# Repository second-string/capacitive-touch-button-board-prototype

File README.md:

# capacitive-touch-button-board-prototype

This repo contains two designs for prototype PCBs for testing different capacitive touch button styles and different reverse-mounted LED colors and styles. While version 1.1 was indeed fabbed, built, and works, these files are made public only for reference. **Do not expect to build these designs with no changes and have everything working for you**.

Version 1.0 is the full 6x6 version of the board. It all fabrication outputs were generated, but the board was never fabbed due to cost.
Version 1.1 is the same as 1.0 but with the top 3 rows of buttons removed to simplify the design physical size and part cost.   

There is a schematic PDF and PCB layer prints PDF in the version 1.1 directory if you do not have KiCad. Version 1.1 that was built also contains generated Excel and interactive boms in its main directory or the `bom/` directory.

Find the custom capacitive touch footprints in the `symbols_and_footprints/` directory of each hardware version.

There is test firmware for version 1.1 in `button-board_rev_1_1/bringup_firmware/`. **NOTE:** This firmware is sloppy, terribly written, inefficient, and everything is hardcoded. It is only included as a reference, do not think that this will work for you out of the box.

Videos of example behavior are in the `img/` directory.

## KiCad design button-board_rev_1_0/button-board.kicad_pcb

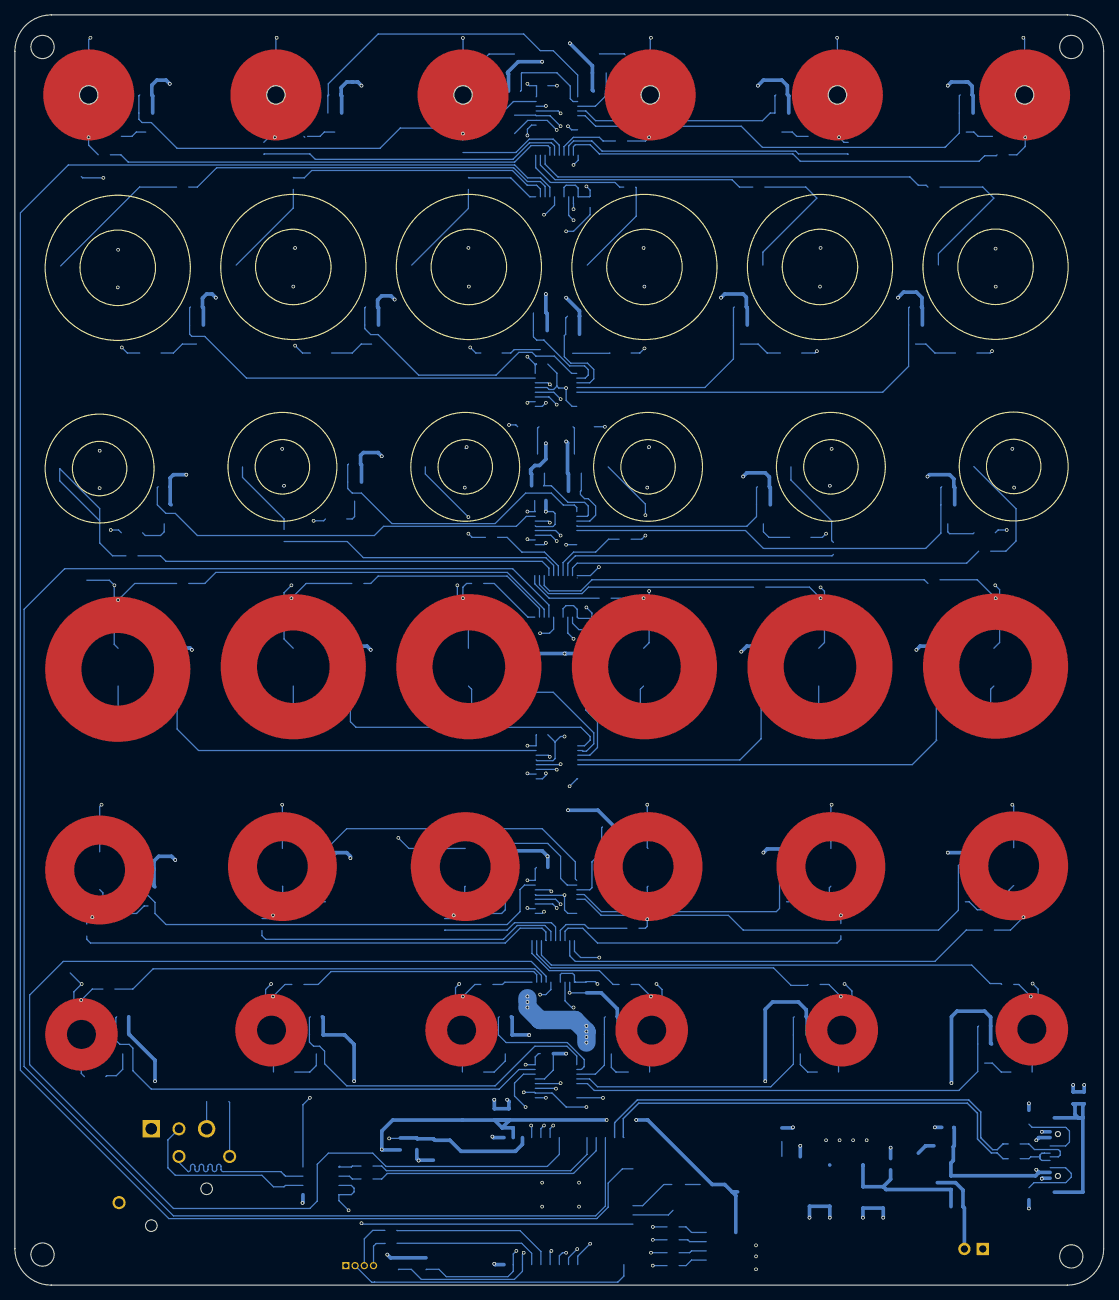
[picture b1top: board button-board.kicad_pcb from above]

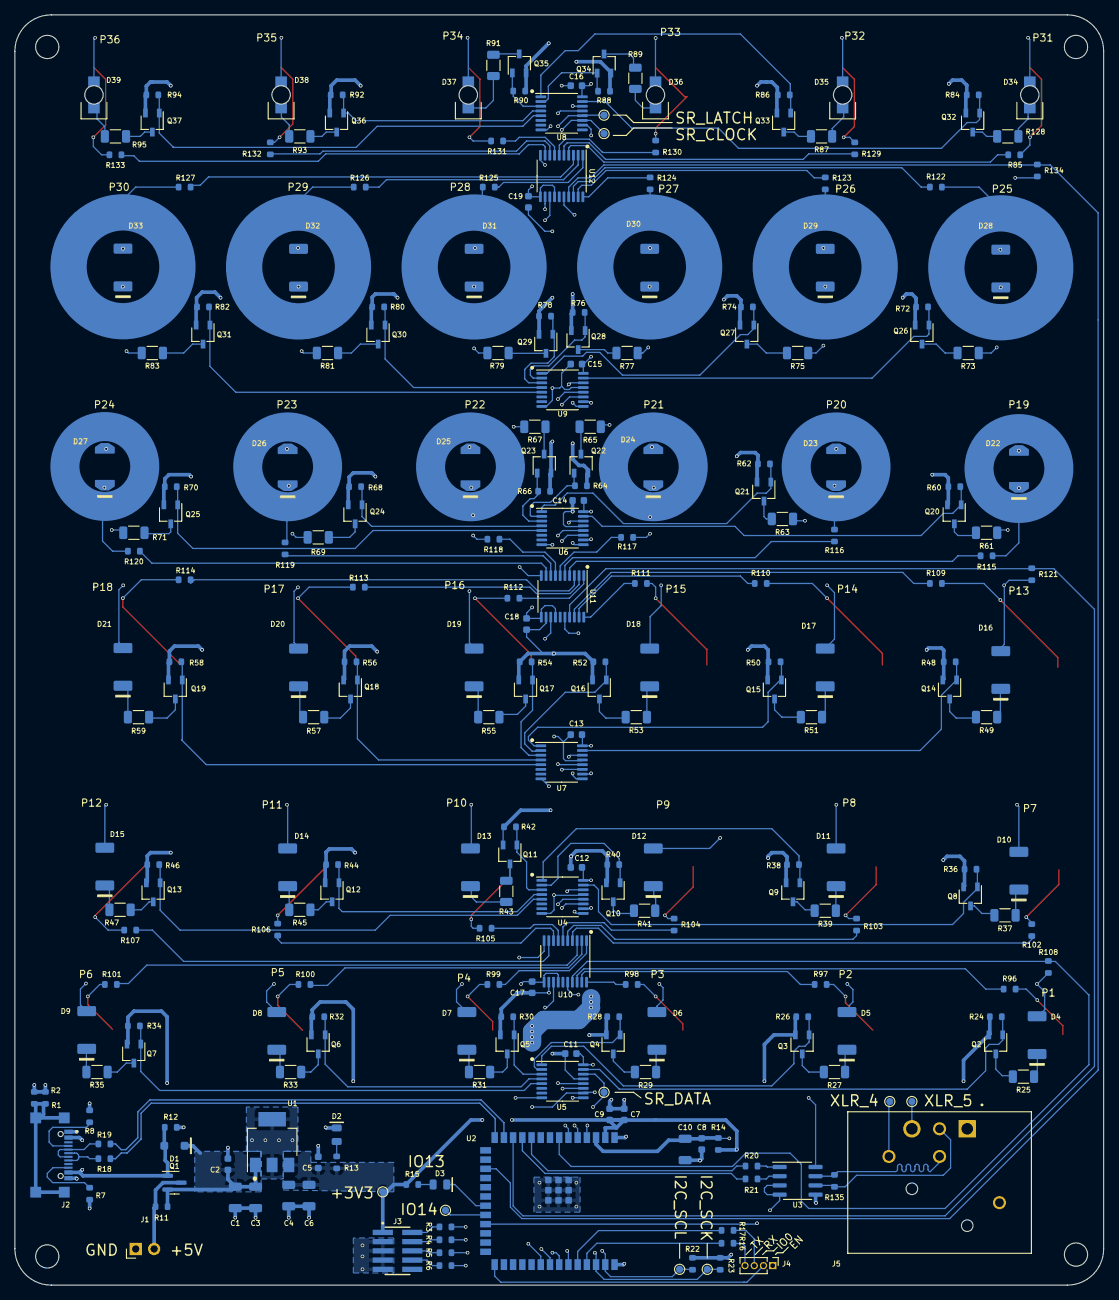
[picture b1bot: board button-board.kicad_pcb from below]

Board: 4 copper layers, 150.0 x 175.0 mm, 294 parts (254 on the bottom side), 232 nets.

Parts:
C1, C3, C6, C10: 10uF; C_1206_3216Metric
C2, C5, C9: 1uF; C_0603_1608Metric
C4: 22uF; C_1206_3216Metric
C7, C8, C11, C12, C13, C14, C15, C16, C17, C18, C19: 0.1uF; C_0603_1608Metric
D1: D; D_SOD-123F
D2, D3: LED; D_0805_2012Metric
D4, D5, D6, D7, D8, D9, D10, D11, D12, D13, D14, D15, D16, D17, D18, D19, D20, D21, D28, D29, D30, D31, D32, D33: LED; LED_SunLED_XZ_Reverse_Mount
D22, D23, D24, D25, D26, D27: LED; LED_SunLED_XZ_Reverse_Mount_Cut_Pads
D34, D35, D36, D37, D38, D39: LED; LED_LTST-C230K
H1, H2, H3, H4: MountingHole; MountingHole_3.2mm_M3
J1: Screw_Terminal_01x02; PinHeader_1x02_P2.54mm_Horizontal
J2: USB_C_Receptacle_USB2.0_EDITED; AMPHENOL_GSB1C41110SSHR
J3: FTSH-105-01-S-DV-TR; SAMTEC_FTSH-105-01-S-DV-TR
J4: Conn_01x04; PinHeader_1x04_P1.27mm_Vertical
J5: XLR5_Ground; NEUTRIK_NC5FAH
P1, P2, P3, P4, P5, P6: Cap_Touch_Ring_Small
P7, P8, P9, P10, P11, P12: Cap_Touch_Ring_Medium
P13, P14, P15, P16, P17, P18: Cap_Touch_Ring_Large
P19, P20, P21, P22, P23, P24: Cap_Touch_Ring_Medium_Bottom
P25, P26, P27, P28, P29, P30: Cap_Touch_Ring_Large_Bottom
P31, P32, P33, P34, P35, P36: Cap_Touch_Ring_Cutout
Q1: PMOS; SOT-23
Q2, Q3, Q4, Q5, Q6, Q7, Q8, Q9, Q10, Q11, Q12, Q13, Q14, Q15, Q16, Q17, Q18, Q19, Q20, Q21, Q22, Q23, Q24, Q25, Q26, Q27, Q28, Q29, Q30, Q31, Q32, Q33, Q34, Q35, Q36, Q37: NMOS; TSOT-23
R1, R2, R11, R16, R17, R18, R19, R20, R21: 0R; R_0603_1608Metric
R3, R4, R5, R6: R; R_0603_1608Metric
R7, R8: 5k1; R_0603_1608Metric
R12: 100k; R_0603_1608Metric
R13, R15: 3.3k-8k; R_0603_1608Metric
R14, R22, R23, R24, R26, R28, R30, R32, R34, R36, R38, R40, R42, R44, R46, R48, R50, R52, R54, R56, R58, R60, R62, R64, R66, R68, R70, R72, R74, R76, R78, R80, R82, R84, R86, R88, R90, R92, R94, R96, R97, R98, R99, R100, R101, R102, R103, R104, R105, R106, R107, R109, R110, R111, R112, R113, R114, R115, R116, R117, R118, R119, R120, R122, R123, R124, R125, R126, R127, R128, R129, R130, R131, R132, R133: 10k; R_0603_1608Metric
R25, R27, R29, R31, R33, R35, R37, R39, R41, R43, R45, R47, R49, R51, R53, R55, R57, R59, R61, R63, R65, R67, R69, R71, R73, R75, R77, R79, R81, R83, R85, R87, R89, R91, R93, R95: 470R 1/2W; R_1206_3216Metric
R108, R121, R134: 47k; R_0603_1608Metric
R135: 120R; R_0603_1608Metric
TP1, TP2: TestPoint; TestPoint_Pad_D1.0mm
TP3: 3V3; TestPoint_Pad_D1.0mm
TP4: IO14; TestPoint_Pad_D1.0mm
TP5: LATCH; TestPoint_Pad_D1.0mm
TP6: CLOCK; TestPoint_Pad_D1.0mm
TP7: DATA; TestPoint_Pad_D1.0mm
TP8: SCL; TestPoint_Pad_D1.0mm
TP9: SCK; TestPoint_Pad_D1.0mm
U1: AZ1117CH2-3.3; SOT-223
U2: ESP32-S3-WROOM-1
U3: SP3485CN; SOIC-8_3.9x4.9mm_P1.27mm
U4, U5, U6, U7, U8, U9: 74HC595; TSSOP-16_4.4x5mm_P0.65mm
U10, U11, U12: AT42QT2120-SU; TSSOP-20_4.4x6.5mm_P0.65mm

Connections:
+3V3: C4.1, C5.1, C6.1, C7.1, C9.1, J3.01, R13.1, R14.1, R15.1, R22.1, R23.1, TP3.1, U1.3 (VO), U2.2 (3V3)
+5V: C11.1, C12.1, C13.1, C14.1, C15.1, C16.1, C17.1, C18.1, C19.1, D4.2 (A), D5.2 (A), D6.2 (A), D7.2 (A), D8.2 (A), D9.2 (A), D10.2 (A), D11.2 (A), D12.2 (A), D13.2 (A), D14.2 (A), D15.2 (A), D16.2 (A), D17.2 (A), D18.2 (A), D19.2 (A), D20.2 (A), D21.2 (A), D22.2 (A), D23.2 (A), D24.2 (A), D25.2 (A), D26.2 (A), D27.2 (A), D28.2 (A), D29.2 (A), D30.2 (A), D31.2 (A), D32.2 (A), D33.2 (A), D34.2 (A), D35.2 (A), D36.2 (A), D37.2 (A), D38.2 (A), D39.2 (A), J1.2, Q1.3 (D), R11.1, R108.1, R121.1, R134.1, U3.8 (VCC), U4.10 (~SRCLR), U4.16 (VCC), U5.10 (~SRCLR), U5.16 (VCC), U6.10 (~SRCLR), U6.16 (VCC), U7.10 (~SRCLR), U7.16 (VCC), U8.10 (~SRCLR), U8.16 (VCC), U9.10 (~SRCLR), U9.16 (VCC), U10.11 (VDD), U10.14 (~RESET), U11.11 (VDD), U11.14 (~RESET), U12.11 (VDD), U12.14 (~RESET)
/control/CAP_CHANGE.0: R108.2, U2.7 (GPIO7/TOUCH7/ADC1_CH6), U10.17 (~CHANGE)
/control/CAP_CHANGE.1: R121.2, U2.12 (GPIO8/TOUCH8/ADC1_CH7/SUBSPICS1), U11.17 (~CHANGE)
/control/CAP_CHANGE.2: R134.2, U2.17 (GPIO9/TOUCH9/ADC1_CH8/FSPIHD/SUBSPIHD), U12.17 (~CHANGE)
/control/DMX.N: J5.2, R135.1, U3.7 (B)
/control/DMX.P: J5.3, R135.2, U3.6 (A)
/control/ESP_IO13: D3.1 (K), U2.21 (GPIO13/TOUCH13/ADC2_CH2/FSPIQ/FSPIIO7/S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)
/control/ESP_IO14: TP4.1, U2.22 (GPIO14/TOUCH14/ADC2_CH3/FSPIWP/FSPIDQS/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)
/control/ESP_PROG.EN: C8.1, C10.1, J4.1, R14.2, U2.3 (EN)
/control/ESP_PROG.IO0: J4.2, U2.27 (GPIO0/BOOT)
/control/ESP_PROG.RX: J4.3, R17.2
/control/ESP_PROG.TX: J4.4, R16.2
/control/I2C.SCK: R23.2, TP9.1, U2.38 (GPIO2/TOUCH2/ADC1_CH1), U10.13 (SDA), U11.13 (SDA), U12.13 (SDA)
/control/I2C.SCL: R22.2, TP8.1, U2.39 (GPIO1/TOUCH1/ADC1_CH0), U10.16 (SCL), U11.16 (SCL), U12.16 (SCL)
/control/JTAG.TCK: R4.1, U2.32 (MTCK/GPIO39/CLK_OUT3/SUBSPICS1)
/control/JTAG.TDI: R6.1, U2.34 (MTDI/GPIO41/CLK_OUT1)
/control/JTAG.TDO: R5.1, U2.33 (MTDO/GPIO40/CLK_OUT2)
/control/JTAG.TMS: R3.1, U2.35 (MTMS/GPIO42)
/control/SR.CLOCK: TP6.1, U2.5 (GPIO5/TOUCH5/ADC1_CH4), U4.11 (SRCLK), U5.11 (SRCLK), U6.11 (SRCLK), U7.11 (SRCLK), U8.11 (SRCLK), U9.11 (SRCLK)
/control/SR.DATA: TP7.1, U2.4 (GPIO4/TOUCH4/ADC1_CH3), U5.14 (SER)
/control/SR.LATCH: TP5.1, U2.6 (GPIO6/TOUCH6/ADC1_CH5), U4.12 (RCLK), U5.12 (RCLK), U6.12 (RCLK), U7.12 (RCLK), U8.12 (RCLK), U9.12 (RCLK)
/control/USB.N: J2.A7 (D-), J2.B7 (D-), R19.2
/control/USB.P: J2.A6 (D+), J2.B6 (D+), R18.2
/control/USB_N: R19.1, U2.13 (GPIO19/U1RTS/ADC2_CH8/CLK_OUT2/USB_D-)
/control/USB_P: R18.1, U2.14 (GPIO20/U1CTS/ADC2_CH9/CLK_OUT1/USB_D+)
/display/led_row_0_1/LED_SER_OUT: U4.9 (QH'), U7.14 (SER)
/display/led_row_2_3/LED_SER_OUT: U6.9 (QH'), U9.14 (SER)
/io/USB_SHIELD_GND: J2.S1 (SHIELD), R1.2, R2.2
/power/5V_COMB: C1.1, C2.1, C3.1, D1.1 (K), Q1.2 (S), R11.2, U1.1 (VI)
GND: C1.2, C2.2, C3.2, C4.2, C5.2, C6.2, C7.2, C8.2, C9.2, C10.2, C11.2, C12.2, C13.2, C14.2, C15.2, C16.2, C17.2, C18.2, C19.2, D2.1 (K), J1.1, J2.A1 (GND), J2.A12 (GND), J2.B1 (GND), J2.B12 (GND), J3.03, J3.05, J3.07, J3.09, J5.1, Q2.2 (S), Q3.2 (S), Q4.2 (S), Q5.2 (S), Q6.2 (S), Q7.2 (S), Q8.2 (S), Q9.2 (S), Q10.2 (S), Q11.2 (S), Q12.2 (S), Q13.2 (S), Q14.2 (S), Q15.2 (S), Q16.2 (S), Q17.2 (S), Q18.2 (S), Q19.2 (S), Q20.2 (S), Q21.2 (S), Q22.2 (S), Q23.2 (S), Q24.2 (S), Q25.2 (S), Q26.2 (S), Q27.2 (S), Q28.2 (S), Q29.2 (S), Q30.2 (S), Q31.2 (S), Q32.2 (S), Q33.2 (S), Q34.2 (S), Q35.2 (S), Q36.2 (S), Q37.2 (S), R1.1, R2.1, R7.2, R8.2, R12.2, R24.2, R26.2, R28.2, R30.2, R32.2, R34.2, R36.2, R38.2, R40.2, R42.2, R44.2, R46.2, R48.2, R50.2, R52.2, R54.2, R56.2, R58.2, R60.2, R62.2, R64.2, R66.2, R68.2, R70.2, R72.2, R74.2, R76.2, R78.2, R80.2, R82.2, R84.2, R86.2, R88.2, R90.2, R92.2, R94.2, U1.2 (GND), U1.4 (GND), U2.1 (GND), U2.40 (GND), U2.41 (GND), U3.5 (GND), U4.8 (GND), U4.13 (~OE), U5.8 (GND), U5.13 (~OE), U6.8 (GND), U6.13 (~OE), U7.8 (GND), U7.13 (~OE), U8.8 (GND), U8.13 (~OE), U9.8 (GND), U9.13 (~OE), U10.10 (VSS), U10.12 (MODE), U11.10 (VSS), U11.12 (MODE), U12.10 (VSS), U12.12 (MODE)
unnamed: D2.2 (A), R13.2
unnamed: D3.2 (A), R15.2
unnamed: D4.1 (K), R25.1
unnamed: D5.1 (K), R27.1
unnamed: D6.1 (K), R29.1
unnamed: D7.1 (K), R31.1
unnamed: D8.1 (K), R33.1
unnamed: D9.1 (K), R35.1
unnamed: D10.1 (K), R37.1
unnamed: D11.1 (K), R39.1
unnamed: D12.1 (K), R41.1
unnamed: D13.1 (K), R43.1
unnamed: D14.1 (K), R45.1
unnamed: D15.1 (K), R47.1
unnamed: D16.1 (K), R49.1
unnamed: D17.1 (K), R51.1
unnamed: D18.1 (K), R53.1
unnamed: D19.1 (K), R55.1
unnamed: D20.1 (K), R57.1
unnamed: D21.1 (K), R59.1
unnamed: D22.1 (K), R61.1
unnamed: D23.1 (K), R63.1
unnamed: D24.1 (K), R65.1
unnamed: D25.1 (K), R67.1
unnamed: D26.1 (K), R69.1
unnamed: D27.1 (K), R71.1
unnamed: D28.1 (K), R73.1
unnamed: D29.1 (K), R75.1
unnamed: D30.1 (K), R77.1
unnamed: D31.1 (K), R79.1
unnamed: D32.1 (K), R81.1
unnamed: D33.1 (K), R83.1
unnamed: D34.1 (K), R85.1
unnamed: D35.1 (K), R87.1
unnamed: D36.1 (K), R89.1
unnamed: D37.1 (K), R91.1
unnamed: D38.1 (K), R93.1
unnamed: D39.1 (K), R95.1
unnamed: J2.A5 (CC1), R8.1
unnamed: J2.B5 (CC2), R7.1
unnamed: J3.02, R3.2
unnamed: J3.04, R4.2
unnamed: J3.06, R5.2
unnamed: J3.08, R6.2
unnamed: J5.4 (P3), TP1.1
unnamed: J5.5, TP2.1
unnamed: P1.1, R96.2
unnamed: P2.1, R97.2
unnamed: P3.1, R98.2
unnamed: P4.1, R99.2
unnamed: P5.1, R100.2
unnamed: P6.1, R101.2
unnamed: P7.1, R102.2
unnamed: P8.1, R103.2
unnamed: P9.1, R104.2
unnamed: P10.1, R105.2
unnamed: P11.1, R106.2
unnamed: P12.1, R107.2
unnamed: P13.1, R109.2
unnamed: P14.1, R110.2
unnamed: P15.1, R111.2
unnamed: P16.1, R112.2
unnamed: P17.1, R113.2
unnamed: P18.1, R114.2
unnamed: P19.1, R115.2
unnamed: P20.1, R116.2
unnamed: P21.1, R117.2
unnamed: P22.1, R118.2
unnamed: P23.1, R119.2
unnamed: P24.1, R120.2
unnamed: P25.1, R122.2
unnamed: P26.1, R123.2
unnamed: P27.1, R124.2
unnamed: P28.1, R125.2
unnamed: P29.1, R126.2
unnamed: P30.1, R127.2
unnamed: P31.1, R128.2
unnamed: P32.1, R129.2
unnamed: P33.1, R130.2
unnamed: P34.1, R131.2
unnamed: P35.1, R132.2
unnamed: P36.1, R133.2
unnamed: Q2.3 (D), R25.2
unnamed: Q2.1 (G), R24.1, U5.15 (QA)
unnamed: Q3.3 (D), R27.2
unnamed: Q3.1 (G), R26.1, U5.1 (QB)
unnamed: Q4.3 (D), R29.2
unnamed: Q4.1 (G), R28.1, U5.2 (QC)
unnamed: Q5.3 (D), R31.2
unnamed: Q5.1 (G), R30.1, U5.3 (QD)
unnamed: Q6.3 (D), R33.2
unnamed: Q6.1 (G), R32.1, U5.4 (QE)
unnamed: Q7.3 (D), R35.2
unnamed: Q7.1 (G), R34.1, U5.5 (QF)
unnamed: Q8.3 (D), R37.2
unnamed: Q8.1 (G), R36.1, U4.15 (QA)
unnamed: Q9.3 (D), R39.2
unnamed: Q9.1 (G), R38.1, U4.1 (QB)
unnamed: Q10.3 (D), R41.2
unnamed: Q10.1 (G), R40.1, U4.2 (QC)
unnamed: Q11.3 (D), R43.2
unnamed: Q11.1 (G), R42.1, U4.3 (QD)
unnamed: Q12.3 (D), R45.2
unnamed: Q12.1 (G), R44.1, U4.4 (QE)
unnamed: Q13.3 (D), R47.2
unnamed: Q13.1 (G), R46.1, U4.5 (QF)
unnamed: Q14.3 (D), R49.2
unnamed: Q14.1 (G), R48.1, U7.15 (QA)
unnamed: Q15.3 (D), R51.2
unnamed: Q15.1 (G), R50.1, U7.1 (QB)
unnamed: Q16.3 (D), R53.2
unnamed: Q16.1 (G), R52.1, U7.2 (QC)
unnamed: Q17.3 (D), R55.2
unnamed: Q17.1 (G), R54.1, U7.3 (QD)
unnamed: Q18.3 (D), R57.2
unnamed: Q18.1 (G), R56.1, U7.4 (QE)
unnamed: Q19.3 (D), R59.2
unnamed: Q19.1 (G), R58.1, U7.5 (QF)
unnamed: Q20.3 (D), R61.2
unnamed: Q20.1 (G), R60.1, U6.15 (QA)
unnamed: Q21.3 (D), R63.2
unnamed: Q21.1 (G), R62.1, U6.1 (QB)
unnamed: Q22.3 (D), R65.2
unnamed: Q22.1 (G), R64.1, U6.2 (QC)
unnamed: Q23.3 (D), R67.2
unnamed: Q23.1 (G), R66.1, U6.3 (QD)
unnamed: Q24.3 (D), R69.2
unnamed: Q24.1 (G), R68.1, U6.4 (QE)
unnamed: Q25.3 (D), R71.2
unnamed: Q25.1 (G), R70.1, U6.5 (QF)
unnamed: Q26.3 (D), R73.2
unnamed: Q26.1 (G), R72.1, U9.15 (QA)
unnamed: Q27.3 (D), R75.2
unnamed: Q27.1 (G), R74.1, U9.1 (QB)
unnamed: Q28.3 (D), R77.2
unnamed: Q28.1 (G), R76.1, U9.2 (QC)
unnamed: Q29.3 (D), R79.2
unnamed: Q29.1 (G), R78.1, U9.3 (QD)
unnamed: Q30.3 (D), R81.2
unnamed: Q30.1 (G), R80.1, U9.4 (QE)
unnamed: Q31.3 (D), R83.2
unnamed: Q31.1 (G), R82.1, U9.5 (QF)
unnamed: Q32.3 (D), R85.2
unnamed: Q32.1 (G), R84.1, U8.15 (QA)
unnamed: Q33.3 (D), R87.2
unnamed: Q33.1 (G), R86.1, U8.1 (QB)
unnamed: Q34.3 (D), R89.2
unnamed: Q34.1 (G), R88.1, U8.2 (QC)
unnamed: Q35.3 (D), R91.2
unnamed: Q35.1 (G), R90.1, U8.3 (QD)
unnamed: Q36.3 (D), R93.2
unnamed: Q36.1 (G), R92.1, U8.4 (QE)
unnamed: Q37.3 (D), R95.2
unnamed: Q37.1 (G), R94.1, U8.5 (QF)
unnamed: R20.1, U2.10 (GPIO17/U1TXD/ADC2_CH6)
unnamed: R21.1, U2.11 (GPIO18/U1RXD/ADC2_CH7/CLK_OUT3)
unnamed: U2.23 (GPIO21), U3.3 (DE), U3.4 (DI)
unnamed: R17.1, U2.36 (U0RXD/GPIO44/CLK_OUT2)
unnamed: R16.1, U2.37 (U0TXD/GPIO43/CLK_OUT1)
unnamed: R20.2, U3.1 (RO)
unnamed: R21.2, U3.2 (~RE)
unnamed: U4.14 (SER), U5.9 (QH')
unnamed: U6.14 (SER), U7.9 (QH')
unnamed: U8.14 (SER), U9.9 (QH')
unnamed: R107.1, U10.9 (KEY0)
unnamed: R106.1, U10.8 (KEY1)
unnamed: R105.1, U10.7 (KEY2/GPO0)
unnamed: R104.1, U10.6 (KEY3/GPO1)
unnamed: R103.1, U10.5 (KEY4/GPO2)
unnamed: R102.1, U10.4 (KEY5/GPO3)
unnamed: R101.1, U10.3 (KEY6/GPO4)
unnamed: R100.1, U10.2 (KEY7/GPO5)
unnamed: R99.1, U10.1 (KEY8/GPO6)
unnamed: R98.1, U10.20 (KEY9/GPO7)
unnamed: R97.1, U10.19 (KEY10/GPO8)
unnamed: R96.1, U10.18 (KEY11/GPO9)
unnamed: R120.1, U11.9 (KEY0)
unnamed: R119.1, U11.8 (KEY1)
unnamed: R118.1, U11.7 (KEY2/GPO0)
unnamed: R117.1, U11.6 (KEY3/GPO1)
unnamed: R116.1, U11.5 (KEY4/GPO2)
unnamed: R115.1, U11.4 (KEY5/GPO3)
unnamed: R114.1, U11.3 (KEY6/GPO4)
unnamed: R113.1, U11.2 (KEY7/GPO5)
unnamed: R112.1, U11.1 (KEY8/GPO6)
unnamed: R111.1, U11.20 (KEY9/GPO7)
unnamed: R110.1, U11.19 (KEY10/GPO8)
unnamed: R109.1, U11.18 (KEY11/GPO9)
unnamed: R133.1, U12.9 (KEY0)
unnamed: R132.1, U12.8 (KEY1)
unnamed: R131.1, U12.7 (KEY2/GPO0)
unnamed: R130.1, U12.6 (KEY3/GPO1)
unnamed: R129.1, U12.5 (KEY4/GPO2)
unnamed: R128.1, U12.4 (KEY5/GPO3)
unnamed: R127.1, U12.3 (KEY6/GPO4)
unnamed: R126.1, U12.2 (KEY7/GPO5)
unnamed: R125.1, U12.1 (KEY8/GPO6)
unnamed: R124.1, U12.20 (KEY9/GPO7)
unnamed: R123.1, U12.19 (KEY10/GPO8)
unnamed: R122.1, U12.18 (KEY11/GPO9)
VBUS: D1.2 (A), J2.A4 (VBUS), J2.A9 (VBUS), J2.B4 (VBUS), J2.B9 (VBUS), Q1.1 (G), R12.1

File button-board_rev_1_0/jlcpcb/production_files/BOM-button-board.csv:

Comment,Designator,Footprint,LCSC
~,P12,Cap_Touch_Ring_Medium,
74HC595,U8,TSSOP-16_4.4x5mm_P0.65mm,
74HC595,U6,TSSOP-16_4.4x5mm_P0.65mm,
74HC595,U5,TSSOP-16_4.4x5mm_P0.65mm,
74HC595,U4,TSSOP-16_4.4x5mm_P0.65mm,
SP3485CN,U3,SOIC-8_3.9x4.9mm_P1.27mm,
ESP32-S3-WROOM-1,U2,ESP32-S3-WROOM-1,
AZ1117CH2-3.3,U1,SOT-223,
SCK,TP9,TestPoint_Pad_D1.0mm,
SCL,TP8,TestPoint_Pad_D1.0mm,
DATA,TP7,TestPoint_Pad_D1.0mm,
CLOCK,TP6,TestPoint_Pad_D1.0mm,
LATCH,TP5,TestPoint_Pad_D1.0mm,
IO14,TP4,TestPoint_Pad_D1.0mm,
3V3,TP3,TestPoint_Pad_D1.0mm,
TestPoint,TP2,TestPoint_Pad_D1.0mm,
TestPoint,TP1,TestPoint_Pad_D1.0mm,
10k,R133,R_0603_1608Metric,
10k,R132,R_0603_1608Metric,
10k,R131,R_0603_1608Metric,
10k,R119,R_0603_1608Metric,
10k,R109,R_0603_1608Metric,
47k,R108,R_0603_1608Metric,
10k,R107,R_0603_1608Metric,
10k,R101,R_0603_1608Metric,
10k,R100,R_0603_1608Metric,
10k,R99,R_0603_1608Metric,
10k,R98,R_0603_1608Metric,
10k,R97,R_0603_1608Metric,
10k,R96,R_0603_1608Metric,
470R 1/2W,R95,R_1206_3216Metric,
470R 1/2W,R91,R_1206_3216Metric,
470R 1/2W,R89,R_1206_3216Metric,
470R 1/2W,R87,R_1206_3216Metric,
470R 1/2W,R85,R_1206_3216Metric,
470R 1/2W,R83,R_1206_3216Metric,
470R 1/2W,R81,R_1206_3216Metric,
470R 1/2W,R79,R_1206_3216Metric,
470R 1/2W,R73,R_1206_3216Metric,
470R 1/2W,R65,R_1206_3216Metric,
470R 1/2W,R59,R_1206_3216Metric,
470R 1/2W,R57,R_1206_3216Metric,
470R 1/2W,R55,R_1206_3216Metric,
470R 1/2W,R53,R_1206_3216Metric,
470R 1/2W,R51,R_1206_3216Metric,
470R 1/2W,R49,R_1206_3216Metric,
470R 1/2W,R47,R_1206_3216Metric,
470R 1/2W,R45,R_1206_3216Metric,
470R 1/2W,R43,R_1206_3216Metric,
470R 1/2W,R41,R_1206_3216Metric,
470R 1/2W,R39,R_1206_3216Metric,
470R 1/2W,R37,R_1206_3216Metric,
470R 1/2W,R35,R_1206_3216Metric,
470R 1/2W,R33,R_1206_3216Metric,
470R 1/2W,R31,R_1206_3216Metric,
470R 1/2W,R29,R_1206_3216Metric,
470R 1/2W,R27,R_1206_3216Metric,
470R 1/2W,R25,R_1206_3216Metric,
10k,R23,R_0603_1608Metric,
10k,R22,R_0603_1608Metric,
0R,R21,R_0603_1608Metric,
0R,R20,R_0603_1608Metric,
0R,R19,R_0603_1608Metric,
0R,R18,R_0603_1608Metric,
0R,R17,R_0603_1608Metric,
0R,R16,R_0603_1608Metric,
3.3k-8k,R15,R_0603_1608Metric,
10k,R14,R_0603_1608Metric,
3.3k-8k,R13,R_0603_1608Metric,
100k,R12,R_0603_1608Metric,
5k1,R8,R_0603_1608Metric,
5k1,R7,R_0603_1608Metric,
R,R6,R_0603_1608Metric,
R,R5,R_0603_1608Metric,
R,R4,R_0603_1608Metric,
R,R3,R_0603_1608Metric,
NMOS,Q37,TSOT-23,
NMOS,Q18,TSOT-23,
NMOS,Q17,TSOT-23,
NMOS,Q16,TSOT-23,
NMOS,Q15,TSOT-23,
NMOS,Q14,TSOT-23,
NMOS,Q13,TSOT-23,
NMOS,Q12,TSOT-23,
NMOS,Q11,TSOT-23,
NMOS,Q10,TSOT-23,
NMOS,Q9,TSOT-23,
NMOS,Q8,TSOT-23,
NMOS,Q7,TSOT-23,
NMOS,Q6,TSOT-23,
NMOS,Q5,TSOT-23,
NMOS,Q4,TSOT-23,
NMOS,Q3,TSOT-23,
NMOS,Q2,TSOT-23,
PMOS,Q1,SOT-23,
~,P36,Cap_Touch_Ring_Cutout,
~,P35,Cap_Touch_Ring_Cutout,
~,P34,Cap_Touch_Ring_Cutout,
~,P33,Cap_Touch_Ring_Cutout,
~,P32,Cap_Touch_Ring_Cutout,
~,P31,Cap_Touch_Ring_Cutout,
~,P30,Cap_Touch_Ring_Large_Bottom,
~,P29,Cap_Touch_Ring_Large_Bottom,
~,P28,Cap_Touch_Ring_Large_Bottom,
~,P27,Cap_Touch_Ring_Large_Bottom,
~,P26,Cap_Touch_Ring_Large_Bottom,
~,P25,Cap_Touch_Ring_Large_Bottom,
~,P24,Cap_Touch_Ring_Medium_Bottom,
~,P23,Cap_Touch_Ring_Medium_Bottom,
~,P22,Cap_Touch_Ring_Medium_Bottom,
~,P21,Cap_Touch_Ring_Medium_Bottom,
~,P20,Cap_Touch_Ring_Medium_Bottom,
~,P19,Cap_Touch_Ring_Medium_Bottom,
~,P18,Cap_Touch_Ring_Large,
~,P17,Cap_Touch_Ring_Large,
~,P16,Cap_Touch_Ring_Large,
~,P15,Cap_Touch_Ring_Large,
~,P14,Cap_Touch_Ring_Large,
~,P13,Cap_Touch_Ring_Large,
~,P11,Cap_Touch_Ring_Medium,
~,P10,Cap_Touch_Ring_Medium,
~,P9,Cap_Touch_Ring_Medium,
~,P8,Cap_Touch_Ring_Medium,
~,P7,Cap_Touch_Ring_Medium,
~,P6,Cap_Touch_Ring_Small,
~,P5,Cap_Touch_Ring_Small,
~,P4,Cap_Touch_Ring_Small,
~,P3,Cap_Touch_Ring_Small,
~,P2,Cap_Touch_Ring_Small,
~,P1,Cap_Touch_Ring_Small,
XLR5_Ground,J5,NEUTRIK_NC5FAH,
Conn_01x04,J4,PinHeader_1x04_P1.27mm_Vertical,
FTSH-105-01-S-DV-TR,J3,SAMTEC_FTSH-105-01-S-DV-TR,
USB_C_Receptacle_USB2.0_EDITED,J2,AMPHENOL_GSB1C41110SSHR,
Screw_Terminal_01x02,J1,PinHeader_1x02_P2.54mm_Horizontal,
LED,D39,LED_LTST-C230K,
LED,D38,LED_LTST-C230K,
LED,D37,LED_LTST-C230K,
LED,D18,LED_SunLED_XZ_Reverse_Mount,
LED,D17,LED_SunLED_XZ_Reverse_Mount,
LED,D16,LED_SunLED_XZ_Reverse_Mount,
LED,D15,LED_SunLED_XZ_Reverse_Mount,
LED,D14,LED_SunLED_XZ_Reverse_Mount,
LED,D13,LED_SunLED_XZ_Reverse_Mount,
LED,D12,LED_SunLED_XZ_Reverse_Mount,
LED,D11,LED_SunLED_XZ_Reverse_Mount,
LED,D10,LED_SunLED_XZ_Reverse_Mount,
LED,D9,LED_SunLED_XZ_Reverse_Mount,
LED,D8,LED_SunLED_XZ_Reverse_Mount,
LED,D7,LED_SunLED_XZ_Reverse_Mount,
LED,D6,LED_SunLED_XZ_Reverse_Mount,
LED,D5,LED_SunLED_XZ_Reverse_Mount,
LED,D4,LED_SunLED_XZ_Reverse_Mount,
LED,D3,D_0805_2012Metric,
LED,D2,D_0805_2012Metric,
D,D1,D_SOD-123F,
10uF,C10,C_1206_3216Metric,
1uF,C9,C_0603_1608Metric,
0.1uF,C8,C_0603_1608Metric,
0.1uF,C7,C_0603_1608Metric,
10uF,C6,C_1206_3216Metric,
1uF,C5,C_0603_1608Metric,
22uF,C4,C_1206_3216Metric,
10uF,C3,C_1206_3216Metric,
1uF,C2,C_0603_1608Metric,
10uF,C1,C_1206_3216Metric,
120R,R135,R_0603_1608Metric,
NMOS,Q34,TSOT-23,
10k,R106,R_0603_1608Metric,
AT42QT2120-SU,U12,TSSOP-20_4.4x6.5mm_P0.65mm,
47k,R134,R_0603_1608Metric,
10k,R130,R_0603_1608Metric,
10k,R129,R_0603_1608Metric,
10k,R128,R_0603_1608Metric,
10k,R127,R_0603_1608Metric,
10k,R126,R_0603_1608Metric,
10k,R125,R_0603_1608Metric,
10k,R124,R_0603_1608Metric,
10k,R123,R_0603_1608Metric,
10k,R122,R_0603_1608Metric,
74HC595,U9,TSSOP-16_4.4x5mm_P0.65mm,
74HC595,U7,TSSOP-16_4.4x5mm_P0.65mm,
AT42QT2120-SU,U10,TSSOP-20_4.4x6.5mm_P0.65mm,
AT42QT2120-SU,U11,TSSOP-20_4.4x6.5mm_P0.65mm,
470R 1/2W,R93,R_1206_3216Metric,
470R 1/2W,R71,R_1206_3216Metric,
470R 1/2W,R69,R_1206_3216Metric,
470R 1/2W,R67,R_1206_3216Metric,
470R 1/2W,R63,R_1206_3216Metric,
470R 1/2W,R61,R_1206_3216Metric,
10k,R105,R_0603_1608Metric,
10k,R104,R_0603_1608Metric,
10k,R103,R_0603_1608Metric,
10k,R102,R_0603_1608Metric,
470R 1/2W,R77,R_1206_3216Metric,
470R 1/2W,R75,R_1206_3216Metric,
47k,R121,R_0603_1608Metric,
10k,R120,R_0603_1608Metric,
10k,R118,R_0603_1608Metric,
10k,R117,R_0603_1608Metric,
10k,R116,R_0603_1608Metric,
10k,R115,R_0603_1608Metric,
10k,R114,R_0603_1608Metric,
10k,R113,R_0603_1608Metric,
10k,R112,R_0603_1608Metric,
10k,R111,R_0603_1608Metric,
10k,R110,R_0603_1608Metric,
NMOS,Q36,TSOT-23,
NMOS,Q35,TSOT-23,
NMOS,Q33,TSOT-23,
NMOS,Q32,TSOT-23,
NMOS,Q25,TSOT-23,
NMOS,Q24,TSOT-23,
NMOS,Q23,TSOT-23,
NMOS,Q22,TSOT-23,
NMOS,Q21,TSOT-23,
NMOS,Q20,TSOT-23,
NMOS,Q31,TSOT-23,
NMOS,Q30,TSOT-23,
NMOS,Q29,TSOT-23,
NMOS,Q28,TSOT-23,
NMOS,Q27,TSOT-23,
NMOS,Q26,TSOT-23,
NMOS,Q19,TSOT-23,
LED,D36,LED_LTST-C230K,
LED,D35,LED_LTST-C230K,
LED,D34,LED_LTST-C230K,
LED,D27,LED_SunLED_XZ_Reverse_Mount_Cut_Pads,
LED,D26,LED_SunLED_XZ_Reverse_Mount_Cut_Pads,
LED,D25,LED_SunLED_XZ_Reverse_Mount_Cut_Pads,
LED,D24,LED_SunLED_XZ_Reverse_Mount_Cut_Pads,
LED,D23,LED_SunLED_XZ_Reverse_Mount_Cut_Pads,
LED,D22,LED_SunLED_XZ_Reverse_Mount_Cut_Pads,
LED,D33,LED_SunLED_XZ_Reverse_Mount,
LED,D32,LED_SunLED_XZ_Reverse_Mount,
LED,D31,LED_SunLED_XZ_Reverse_Mount,
LED,D30,LED_SunLED_XZ_Reverse_Mount,
LED,D29,LED_SunLED_XZ_Reverse_Mount,
LED,D28,LED_SunLED_XZ_Reverse_Mount,
LED,D21,LED_SunLED_XZ_Reverse_Mount,
LED,D20,LED_SunLED_XZ_Reverse_Mount,
LED,D19,LED_SunLED_XZ_Reverse_Mount,
MountingHole,H1,MountingHole_3.2mm_M3,
MountingHole,H2,MountingHole_3.2mm_M3,
MountingHole,H3,MountingHole_3.2mm_M3,
MountingHole,H4,MountingHole_3.2mm_M3,
0.1uF,C19,C_0603_1608Metric,
0.1uF,C18,C_0603_1608Metric,
0.1uF,C17,C_0603_1608Metric,
0.1uF,C16,C_0603_1608Metric,
0.1uF,C15,C_0603_1608Metric,
0.1uF,C14,C_0603_1608Metric,
0.1uF,C13,C_0603_1608Metric,
0.1uF,C12,C_0603_1608Metric,
0.1uF,C11,C_0603_1608Metric,

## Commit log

2024-10-19 Initial commit to host files for reference
2024-10-19 Fix readme title
